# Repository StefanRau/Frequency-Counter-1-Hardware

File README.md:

# Frequency-Counter-1-hardware
This repository contains CAD data of Frequency Counter 1

Project repositories are:
- [Project](https://github.com/StefanRau/Frequency-Counter-1-Project)
- [Hardware](https://github.com/StefanRau/Frequency-Counter-1-Hardware)
- [Software](https://github.com/StefanRau/Frequency-Counter-1-Arduino)
- [PC terminal software](https://github.com/StefanRau/Frequency-Counter-1-Terminal)
## Main Board

## Front Plate

## 100 MHz TTL CMOS

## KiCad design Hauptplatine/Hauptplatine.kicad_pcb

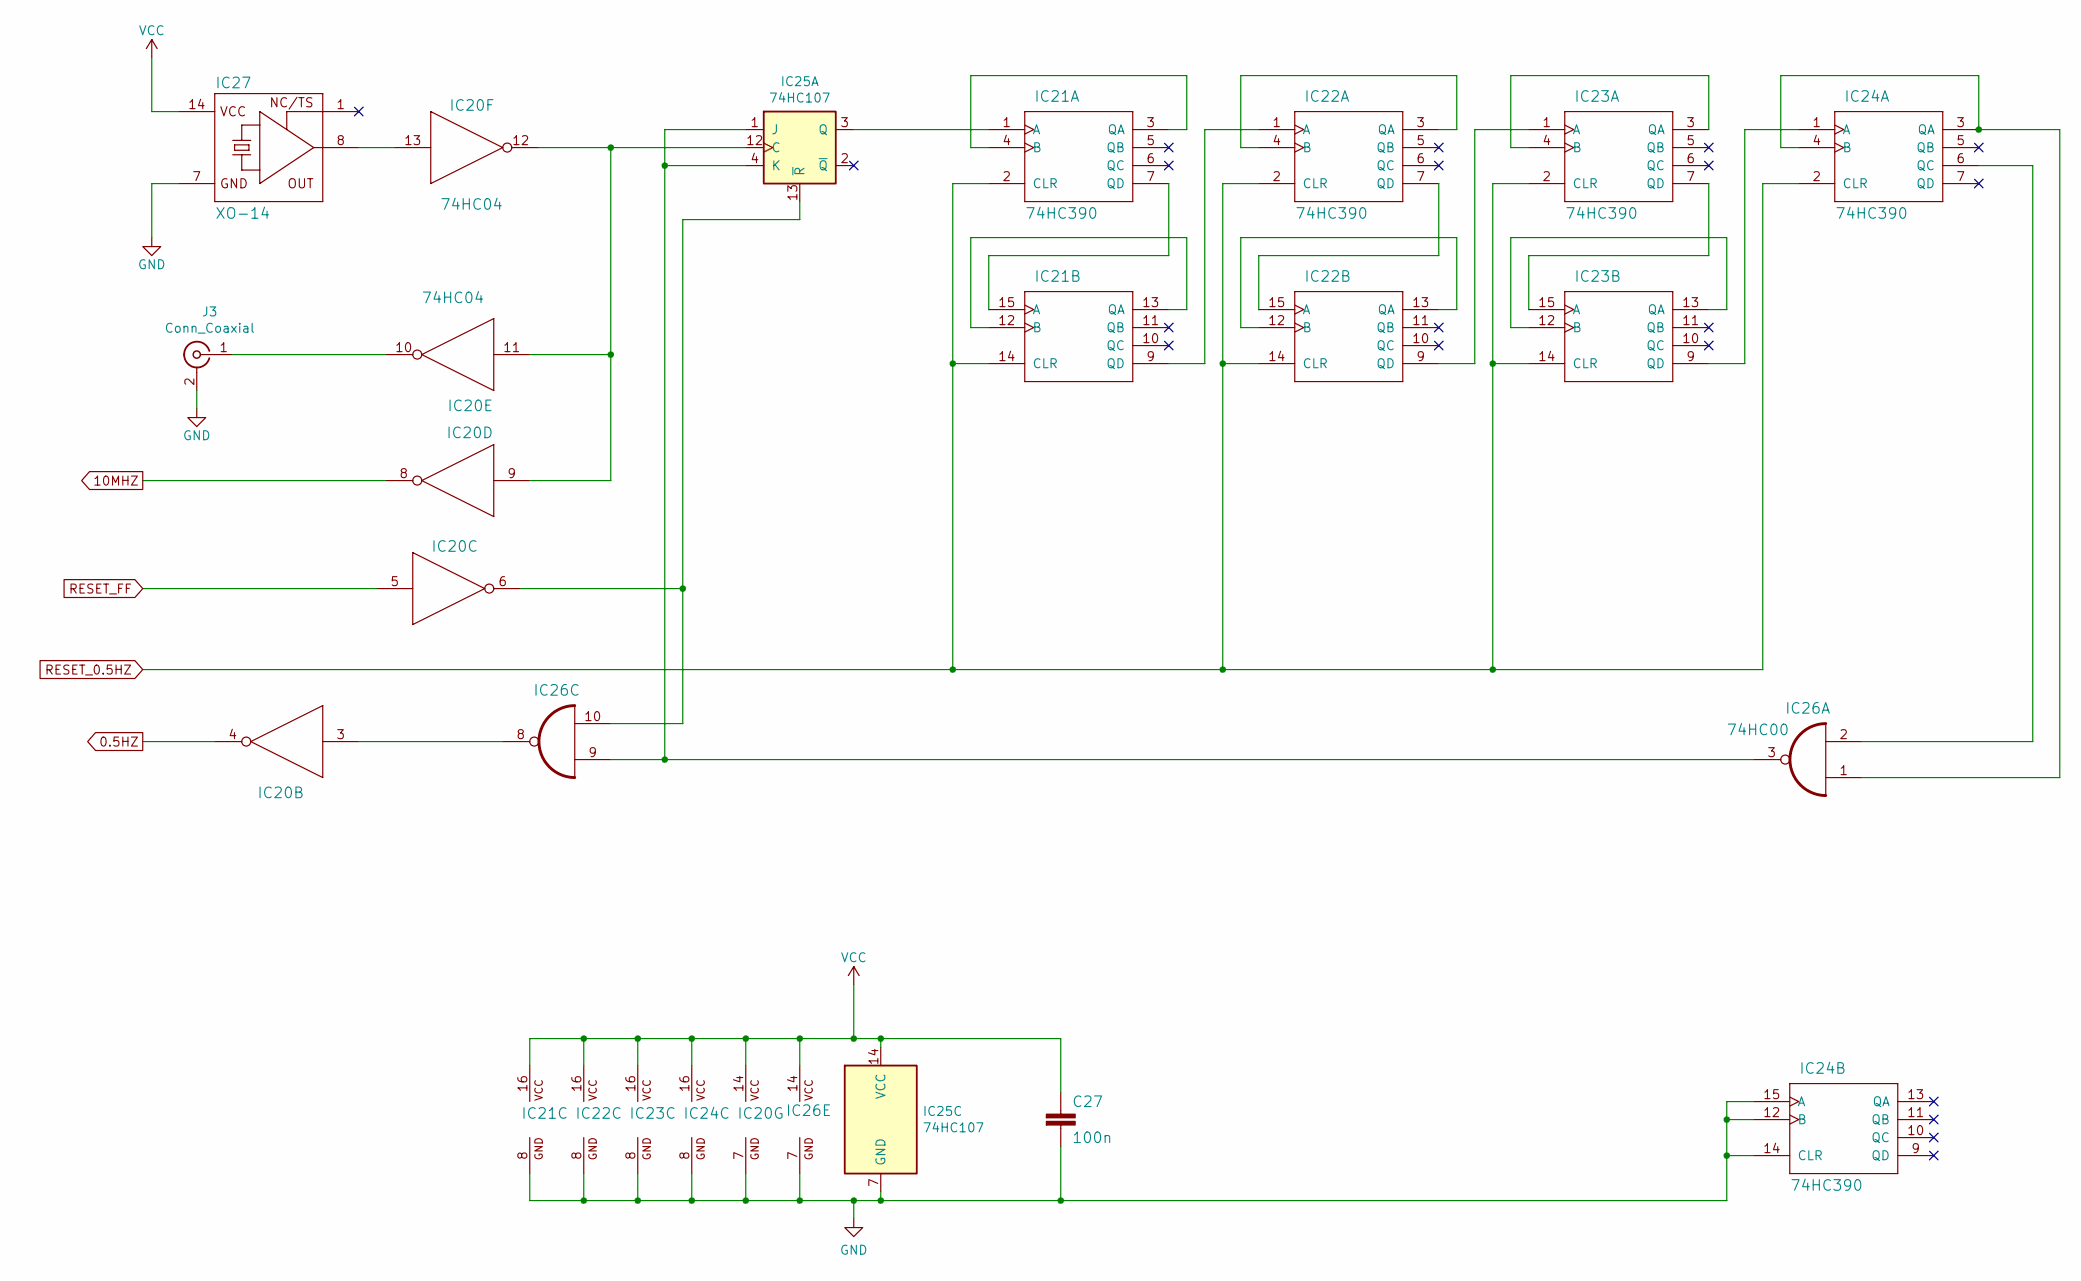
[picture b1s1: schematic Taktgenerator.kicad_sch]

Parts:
C27: 100n; C_Rect_L10.0mm_W4.0mm_P7.50mm_FKS3_FKP3
IC20: 74HC04; DIP-14_W7.62mm_LongPads
IC21, IC22, IC23, IC24: 74HC390; DIP-16_W7.62mm_LongPads
IC25: 74HC107; DIP-14_W7.62mm_LongPads
IC26: 74HC00; DIP-14_W7.62mm_LongPads
IC27: XO-14; Oscillator_DIP-14
J3: Conn_Coaxial; BNC_Amphenol_B6252HB-NPP3G-50_Horizontal

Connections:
0.5HZ: IC20.4 (O); also elsewhere on the board
10MHZ: IC20.8 (O); also elsewhere on the board
unnamed: IC20.3 (I), IC26.8 (O)
unnamed: IC20.6 (O), IC25.13 (~R), IC26.10 (I1)
unnamed: IC20.10 (O), J3.1 (In)
unnamed: IC20.9 (I), IC20.11 (I), IC20.12 (O), IC25.12 (C)
unnamed: IC20.13 (I), IC27.8 (OUT)
unnamed: IC21.1 (A), IC25.3 (Q)
unnamed: IC21.3 (QA), IC21.4 (B)
unnamed: IC21.9 (QD), IC22.1 (A)
unnamed: IC21.12 (B), IC21.13 (QA)
unnamed: IC21.7 (QD), IC21.15 (A)
unnamed: IC22.3 (QA), IC22.4 (B)
unnamed: IC22.9 (QD), IC23.1 (A)
unnamed: IC22.12 (B), IC22.13 (QA)
unnamed: IC22.7 (QD), IC22.15 (A)
unnamed: IC23.3 (QA), IC23.4 (B)
unnamed: IC23.9 (QD), IC24.1 (A)
unnamed: IC23.12 (B), IC23.13 (QA)
unnamed: IC23.7 (QD), IC23.15 (A)
unnamed: IC24.3 (QA), IC24.4 (B), IC26.1 (I0)
unnamed: IC24.6 (QC), IC26.2 (I1)
unnamed: IC25.1 (J), IC25.4 (K), IC26.3 (O), IC26.9 (I0)
RESET_0.5HZ: IC21.2 (CLR), IC21.14 (CLR), IC22.2 (CLR), IC22.14 (CLR), IC23.2 (CLR), IC23.14 (CLR), IC24.2 (CLR); also elsewhere on the board
RESET_FF: IC20.5 (I); also elsewhere on the board
VCC: C27.1, IC20.14 (VCC), IC21.16 (VCC), IC22.16 (VCC), IC23.16 (VCC), IC24.16 (VCC), IC25.14 (VCC), IC26.14 (VCC), IC27.14 (VCC); also elsewhere on the board

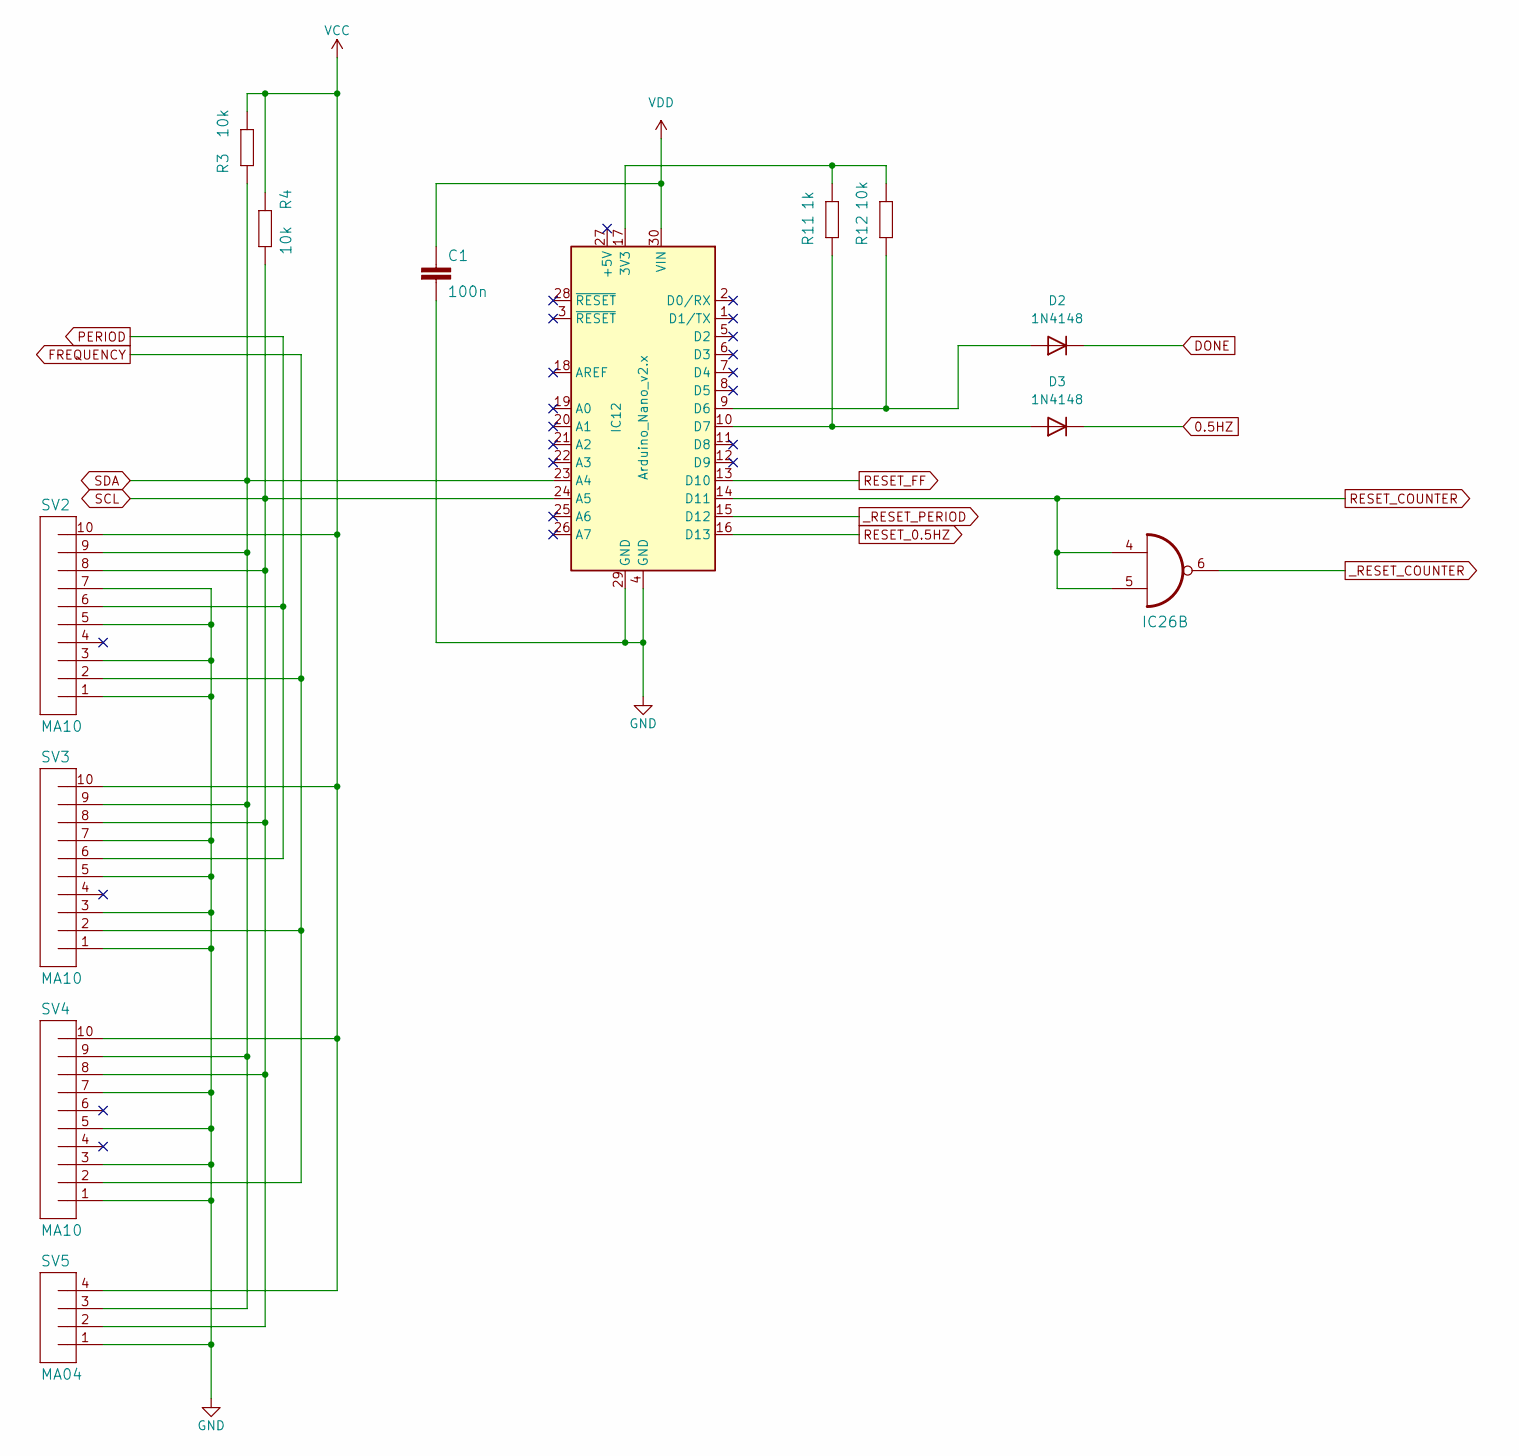
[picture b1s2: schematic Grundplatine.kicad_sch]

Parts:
C1: 100n; C_Rect_L10.0mm_W4.0mm_P7.50mm_FKS3_FKP3
D2, D3: 1N4148; D_DO-35_SOD27_P7.62mm_Horizontal
IC12: Arduino_Nano_v2.x; Arduino_Nano
IC26: 74HC00; DIP-14_W7.62mm_LongPads
R3, R4, R12: 10k; R_Axial_DIN0204_L3.6mm_D1.6mm_P1.90mm_Vertical
R11: 1k; R_Axial_DIN0204_L3.6mm_D1.6mm_P1.90mm_Vertical
SV2, SV3, SV4: MA10; PinSocket_1x10_P2.54mm_Vertical
SV5: MA04; PinSocket_1x04_P2.54mm_Vertical

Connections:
0.5HZ: D3.1 (K); also elsewhere on the board
DONE: D2.1 (K); also elsewhere on the board
FREQUENCY: SV2.2, SV3.2, SV4.2; also elsewhere on the board
unnamed: D2.2 (A), IC12.9 (D6), R12.1
unnamed: D3.2 (A), IC12.10 (D7), R11.1
unnamed: IC12.17 (3V3), R11.2, R12.2
PERIOD: SV2.6, SV3.6; also elsewhere on the board
RESET_0.5HZ: IC12.16 (D13); also elsewhere on the board
RESET_COUNTER: IC12.14 (D11), IC26.4 (I0), IC26.5 (I1); also elsewhere on the board
RESET_FF: IC12.13 (D10); also elsewhere on the board
SCL: IC12.24 (A5), R4.1, SV2.8, SV3.8, SV4.8, SV5.2; also elsewhere on the board
SDA: IC12.23 (A4), R3.1, SV2.9, SV3.9, SV4.9, SV5.3; also elsewhere on the board
VCC: R3.2, R4.2, SV2.10, SV3.10, SV4.10, SV5.4; also elsewhere on the board
VDD: C1.1, IC12.30 (VIN); also elsewhere on the board
_RESET_COUNTER: IC26.6 (O); also elsewhere on the board
_RESET_PERIOD: IC12.15 (D12); also elsewhere on the board

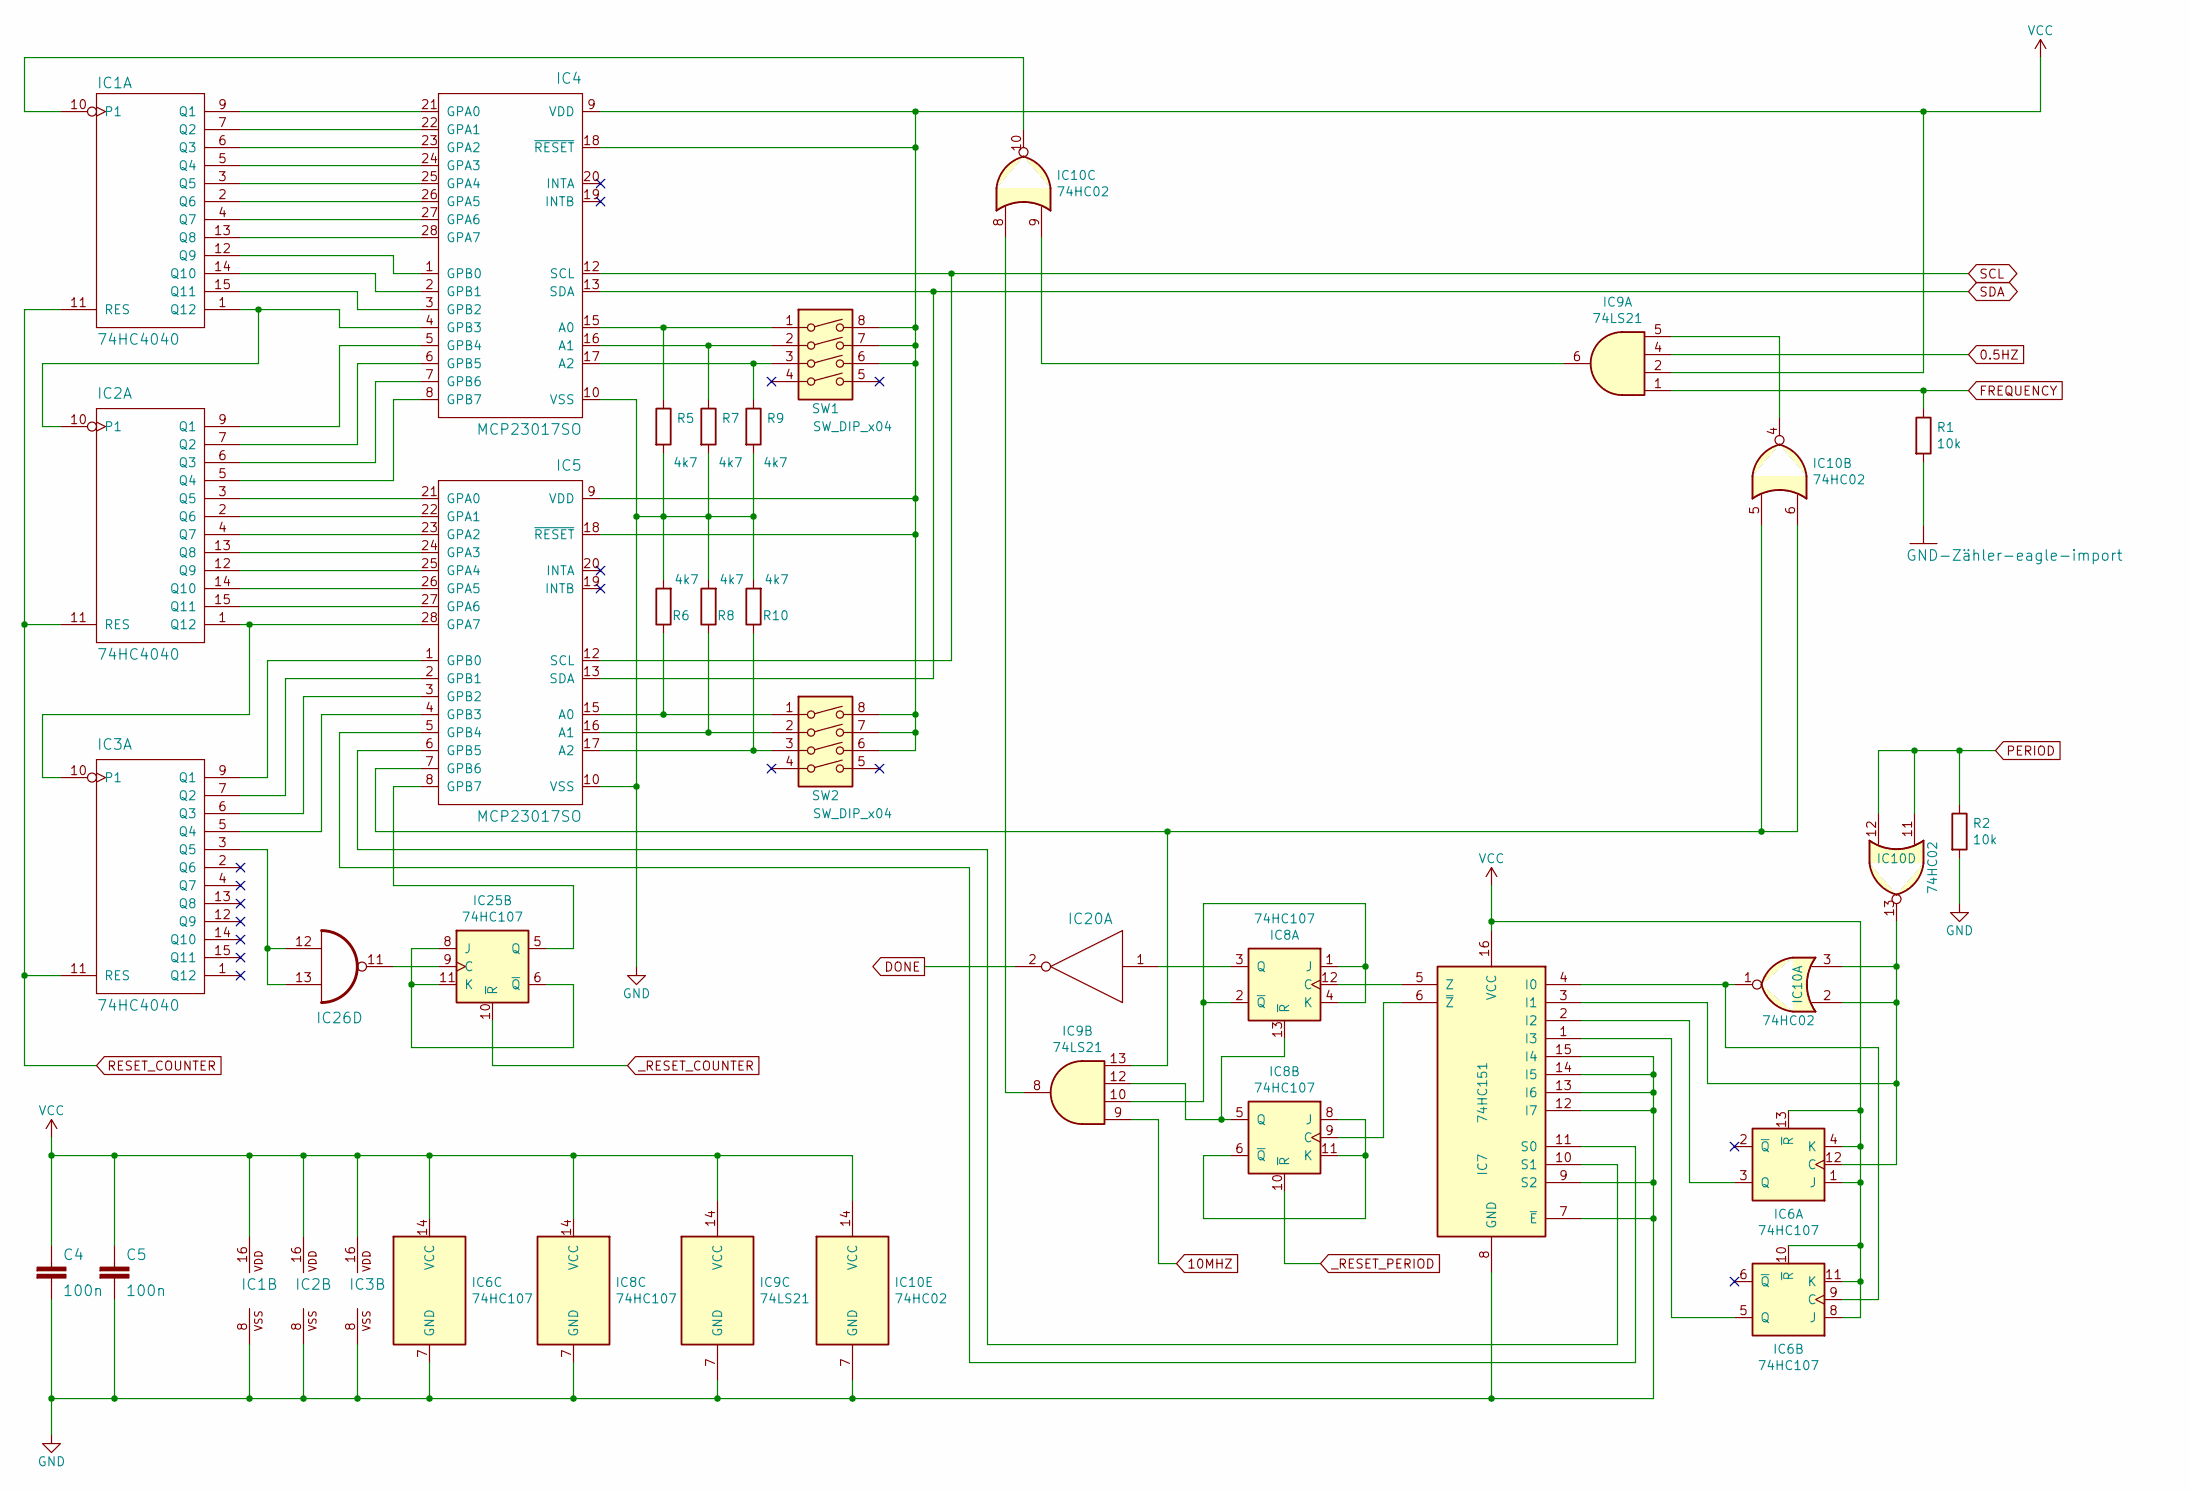
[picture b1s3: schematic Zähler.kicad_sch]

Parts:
C4, C5: 100n; C_Rect_L10.0mm_W4.0mm_P7.50mm_FKS3_FKP3
IC1, IC2, IC3: 74HC4040; DIP-16_W7.62mm_LongPads
IC4, IC5: MCP23017SO; DIP-28_W7.62mm_LongPads
IC6, IC8, IC25: 74HC107; DIP-14_W7.62mm_LongPads
IC7: 74HC151; DIP-16_W7.62mm_LongPads
IC9: 74LS21; DIP-14_W7.62mm_LongPads
IC10: 74HC02; DIP-14_W7.62mm_LongPads
IC20: 74HC04; DIP-14_W7.62mm_LongPads
IC26: 74HC00; DIP-14_W7.62mm_LongPads
R1, R2: 10k; R_Axial_DIN0207_L6.3mm_D2.5mm_P15.24mm_Horizontal
R5, R6, R7, R8, R9, R10: 4k7; R_Axial_DIN0204_L3.6mm_D1.6mm_P1.90mm_Vertical
SW1, SW2: SW_DIP_x04; SW_DIP_SPSTx04_Slide_9.78x12.34mm_W7.62mm_P2.54mm

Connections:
0.5HZ: IC9.4; also elsewhere on the board
10MHZ: IC9.9; also elsewhere on the board
DONE: IC20.2 (O); also elsewhere on the board
FREQUENCY: IC9.1, R1.1; also elsewhere on the board
unnamed: IC1.1 (Q12), IC2.10 (P1), IC4.4 (GPB3)
unnamed: IC1.2 (Q6), IC4.26 (GPA5)
unnamed: IC1.3 (Q5), IC4.25 (GPA4)
unnamed: IC1.4 (Q7), IC4.27 (GPA6)
unnamed: IC1.5 (Q4), IC4.24 (GPA3)
unnamed: IC1.6 (Q3), IC4.23 (GPA2)
unnamed: IC1.7 (Q2), IC4.22 (GPA1)
unnamed: IC1.9 (Q1), IC4.21 (GPA0)
unnamed: IC1.10 (P1), IC10.10
unnamed: IC1.12 (Q9), IC4.1 (GPB0)
unnamed: IC1.13 (Q8), IC4.28 (GPA7)
unnamed: IC1.14 (Q10), IC4.2 (GPB1)
unnamed: IC1.15 (Q11), IC4.3 (GPB2)
unnamed: IC2.1 (Q12), IC3.10 (P1), IC5.28 (GPA7)
unnamed: IC2.2 (Q6), IC5.22 (GPA1)
unnamed: IC2.3 (Q5), IC5.21 (GPA0)
unnamed: IC2.4 (Q7), IC5.23 (GPA2)
unnamed: IC2.5 (Q4), IC4.8 (GPB7)
unnamed: IC2.6 (Q3), IC4.7 (GPB6)
unnamed: IC2.7 (Q2), IC4.6 (GPB5)
unnamed: IC2.9 (Q1), IC4.5 (GPB4)
unnamed: IC2.12 (Q9), IC5.25 (GPA4)
unnamed: IC2.13 (Q8), IC5.24 (GPA3)
unnamed: IC2.14 (Q10), IC5.26 (GPA5)
unnamed: IC2.15 (Q11), IC5.27 (GPA6)
unnamed: IC3.5 (Q4), IC5.4 (GPB3)
unnamed: IC3.6 (Q3), IC5.3 (GPB2)
unnamed: IC3.7 (Q2), IC5.2 (GPB1)
unnamed: IC3.9 (Q1), IC5.1 (GPB0)
unnamed: IC4.15 (A0), R5.1, SW1.1
unnamed: IC4.16 (A1), R7.1, SW1.2
unnamed: IC4.17 (A2), R9.1, SW1.3
unnamed: IC5.5 (GPB4), IC7.11 (S0)
unnamed: IC5.6 (GPB5), IC7.10 (S1)
unnamed: IC5.15 (A0), R6.1, SW2.1
unnamed: IC5.16 (A1), R8.1, SW2.2
unnamed: IC5.17 (A2), R10.1, SW2.3
unnamed: IC6.3 (Q), IC7.2 (I2)
unnamed: IC6.5 (Q), IC7.1 (I3)
unnamed: IC7.5 (Z), IC8.12 (C)
unnamed: IC7.6 (~Z), IC8.9 (C)
unnamed: IC8.1 (J), IC8.2 (~Q), IC8.4 (K), IC9.10
unnamed: IC8.3 (Q), IC20.1 (I)
unnamed: IC8.6 (~Q), IC8.8 (J), IC8.11 (K)
unnamed: IC8.5 (Q), IC8.13 (~R), IC9.12
unnamed: IC6.9 (C), IC7.4 (I0), IC10.1
unnamed: IC9.5, IC10.4
unnamed: IC5.7 (GPB6), IC9.13, IC10.5, IC10.6
unnamed: IC9.8, IC10.8
unnamed: IC9.6, IC10.9
unnamed: IC6.12 (C), IC7.3 (I1), IC10.2, IC10.3, IC10.13
unnamed: IC5.8 (GPB7), IC25.5 (Q)
unnamed: IC25.9 (C), IC26.11 (O)
unnamed: IC25.6 (~Q), IC25.8 (J), IC25.11 (K)
unnamed: IC3.3 (Q5), IC26.12 (I0), IC26.13 (I1)
PERIOD: IC10.11, IC10.12, R2.1; also elsewhere on the board
RESET_COUNTER: IC1.11 (RES), IC2.11 (RES), IC3.11 (RES); also elsewhere on the board
SCL: IC4.12 (SCL), IC5.12 (SCL); also elsewhere on the board
SDA: IC4.13 (SDA), IC5.13 (SDA); also elsewhere on the board
VCC: C4.1, C5.1, IC1.16 (VDD), IC2.16 (VDD), IC3.16 (VDD), IC4.9 (VDD), IC4.18 (~RESET), IC5.9 (VDD), IC5.18 (~RESET), IC6.1 (J), IC6.4 (K), IC6.8 (J), IC6.10 (~R), IC6.11 (K), IC6.13 (~R), IC6.14 (VCC), IC7.16 (VCC), IC8.14 (VCC), IC9.2, IC9.14 (VCC), IC10.14 (VCC), SW1.6, SW1.7, SW1.8, SW2.6, SW2.7, SW2.8; also elsewhere on the board
_RESET_COUNTER: IC25.10 (~R); also elsewhere on the board
_RESET_PERIOD: IC8.10 (~R); also elsewhere on the board

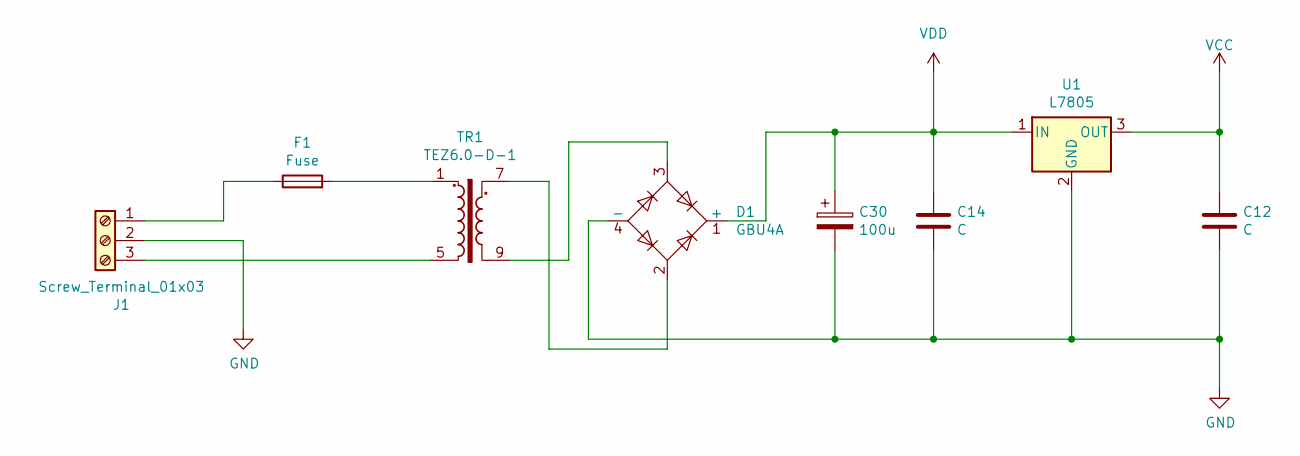
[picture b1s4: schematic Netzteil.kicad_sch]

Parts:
C12, C14: C; C_Rect_L10.0mm_W4.0mm_P7.50mm_FKS3_FKP3
C30: 100u; CP_Radial_D13.0mm_P5.00mm
D1: GBU4A; Diode_Bridge_Vishay_GBU
F1: Fuse; Fuseholder_Cylinder-5x20mm_Schurter_0031_8201_Horizontal_Op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
J1: Screw_Terminal_01x03; TerminalBlock_Phoenix_MKDS-1,5-3-5.08_1x03_P5.08mm_Horizont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
TR1: TEZ6.0-D-1; Transformer_Breve_TEZ-38x45
U1: L7805; TO-220-3_Vertical

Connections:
unnamed: D1.2, TR1.7
unnamed: D1.3, TR1.9
unnamed: F1.1, J1.1
unnamed: F1.2, TR1.1
unnamed: J1.3, TR1.5
VCC: C12.1, U1.3 (OUT); also elsewhere on the board
VDD: C14.1, C30.1, D1.1 (+), U1.1 (IN); also elsewhere on the board

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
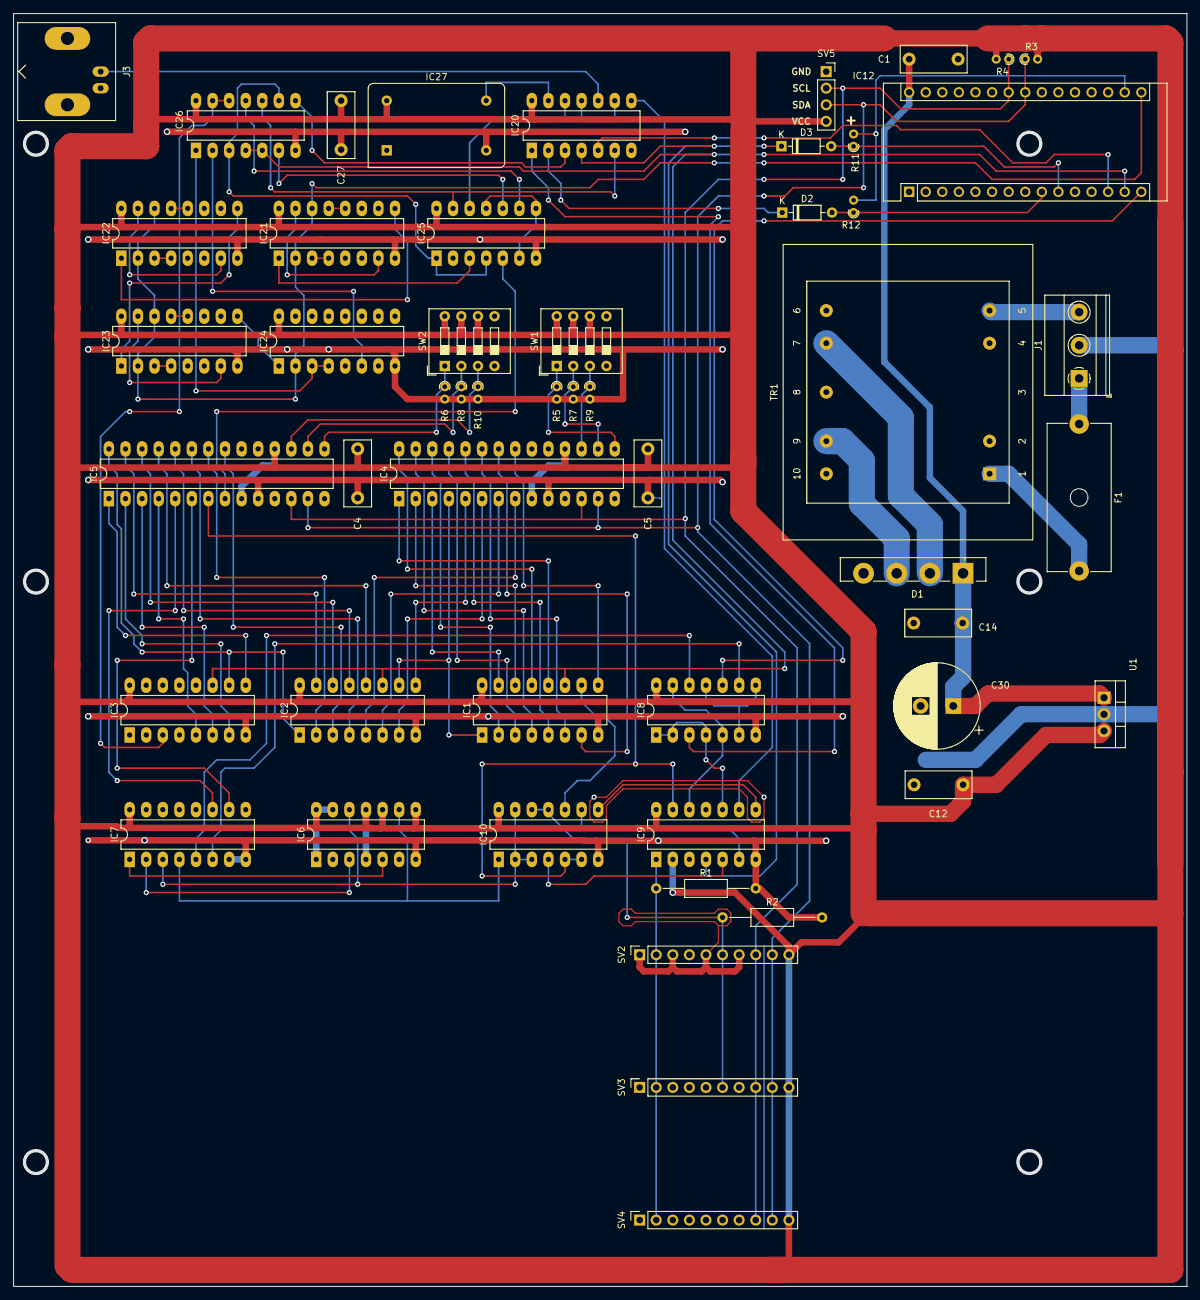
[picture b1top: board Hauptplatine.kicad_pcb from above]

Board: 2 copper layers, 179.7 x 194.9 mm, 52 parts (0 on the bottom side), 99 nets.

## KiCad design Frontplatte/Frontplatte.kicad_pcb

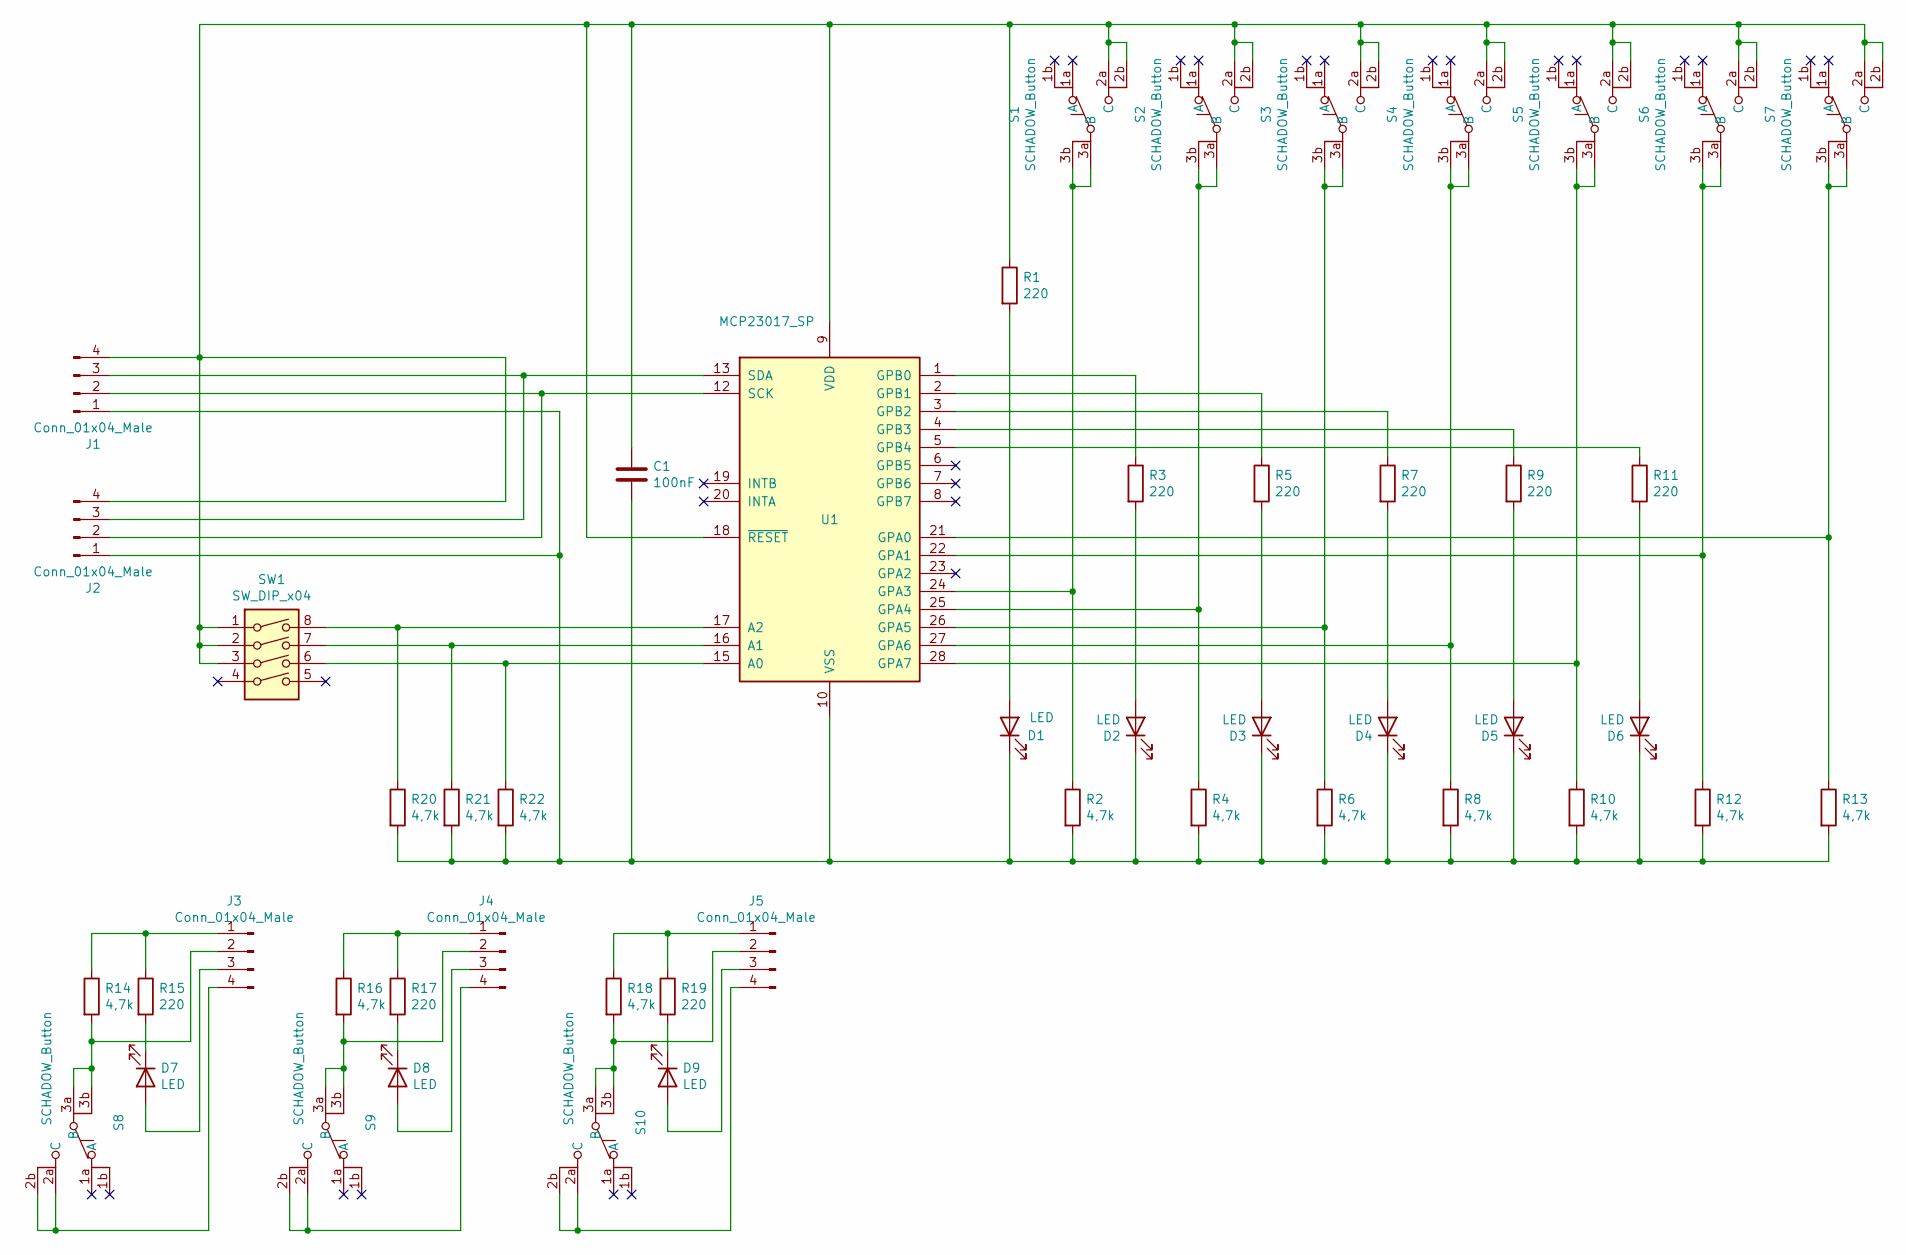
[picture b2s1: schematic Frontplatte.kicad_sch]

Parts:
C1: 100nF; C_Rect_L10.0mm_W4.0mm_P7.50mm_FKS3_FKP3
D1, D2, D3, D4, D5, D6, D7, D8, D9: LED; LED_D5.0mm
J1, J2, J3, J4, J5: Conn_01x04_Male; PinHeader_1x04_P2.54mm_Vertical
R1, R3, R5, R7, R9, R11: 220; R_Axial_DIN0204_L3.6mm_D1.6mm_P7.62mm_Horizontal
R2, R4, R6, R8, R10: 4,7k; R_Axial_DIN0207_L6.3mm_D2.5mm_P15.24mm_Horizontal
R12, R13, R20, R21, R22: 4,7k; R_Axial_DIN0204_L3.6mm_D1.6mm_P7.62mm_Horizontal
R14, R16, R18: 4,7k; R_Axial_DIN0204_L3.6mm_D1.6mm_P1.90mm_Vertical
R15, R17, R19: 220; R_Axial_DIN0204_L3.6mm_D1.6mm_P1.90mm_Vertical
S1, S2, S3, S4, S5, S6, S7, S8, S9, S10: SCHADOW_Button
SW1: SW_DIP_x04; SW_DIP_SPSTx04_Slide_9.78x12.34mm_W7.62mm_P2.54mm
U1: MCP23017_SP; DIP-28_W7.62mm_LongPads

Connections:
unnamed: C1.1, J1.4, J2.4, R1.1, S1.2a (C), S1.2b, S2.2a (C), S2.2b, S3.2a (C), S3.2b, S4.2a (C), S4.2b, S5.2a (C), S5.2b, S6.2a (C), S6.2b, S7.2a (C), S7.2b, SW1.1, SW1.2, SW1.3, U1.9 (VDD), U1.18 (~RESET)
unnamed: C1.2, D1.1 (K), D2.1 (K), D3.1 (K), D4.1 (K), D5.1 (K), D6.1 (K), J1.1, J2.1, R2.2, R4.2, R6.2, R8.2, R10.2, R12.2, R13.2, R20.2, R21.2, R22.2, U1.10 (VSS)
unnamed: D1.2 (A), R1.2
unnamed: D2.2 (A), R3.2
unnamed: D3.2 (A), R5.2
unnamed: D4.2 (A), R7.2
unnamed: D5.2 (A), R9.2
unnamed: D6.2 (A), R11.2
unnamed: D7.1 (K), R15.2
unnamed: D7.2 (A), J3.3
unnamed: D8.1 (K), R17.2
unnamed: D8.2 (A), J4.3
unnamed: D9.1 (K), R19.2
unnamed: D9.2 (A), J5.3
unnamed: J1.2, J2.2, U1.12 (SCK)
unnamed: J1.3, J2.3, U1.13 (SDA)
unnamed: J3.1, R14.1, R15.1
unnamed: J3.2, R14.2, S8.3a (B), S8.3b
unnamed: J3.4, S8.2a (C), S8.2b
unnamed: J4.1, R16.1, R17.1
unnamed: J4.2, R16.2, S9.3a (B), S9.3b
unnamed: J4.4, S9.2a (C), S9.2b
unnamed: J5.1, R18.1, R19.1
unnamed: J5.2, R18.2, S10.3a (B), S10.3b
unnamed: J5.4, S10.2a (C), S10.2b
unnamed: R2.1, S1.3a (B), S1.3b, U1.24 (GPA3)
unnamed: R3.1, U1.1 (GPB0)
unnamed: R4.1, S2.3a (B), S2.3b, U1.25 (GPA4)
unnamed: R5.1, U1.2 (GPB1)
unnamed: R6.1, S3.3a (B), S3.3b, U1.26 (GPA5)
unnamed: R7.1, U1.3 (GPB2)
unnamed: R8.1, S4.3a (B), S4.3b, U1.27 (GPA6)
unnamed: R9.1, U1.4 (GPB3)
unnamed: R10.1, S5.3a (B), S5.3b, U1.28 (GPA7)
unnamed: R11.1, U1.5 (GPB4)
unnamed: R12.1, S6.3a (B), S6.3b, U1.22 (GPA1)
unnamed: R13.1, S7.3a (B), S7.3b, U1.21 (GPA0)
unnamed: R20.1, SW1.8, U1.17 (A2)
unnamed: R21.1, SW1.7, U1.16 (A1)
unnamed: R22.1, SW1.6, U1.15 (A0)

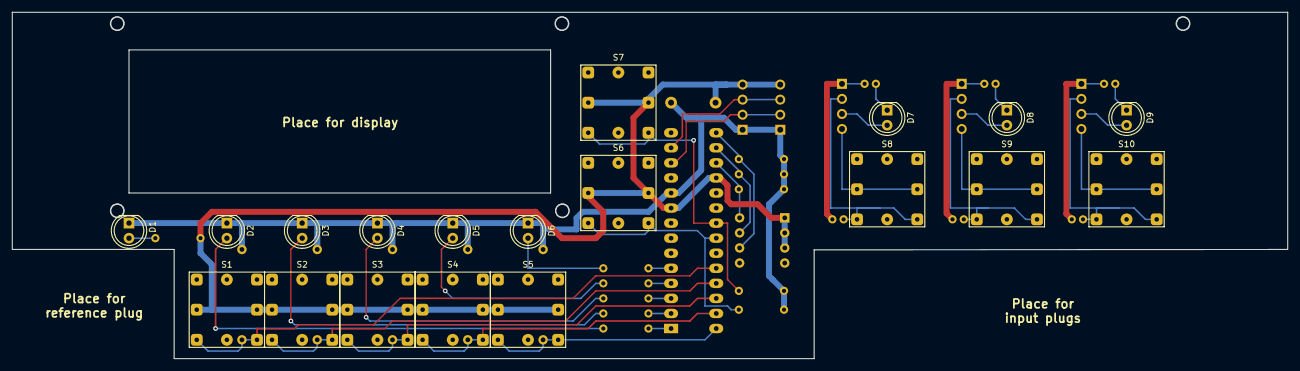
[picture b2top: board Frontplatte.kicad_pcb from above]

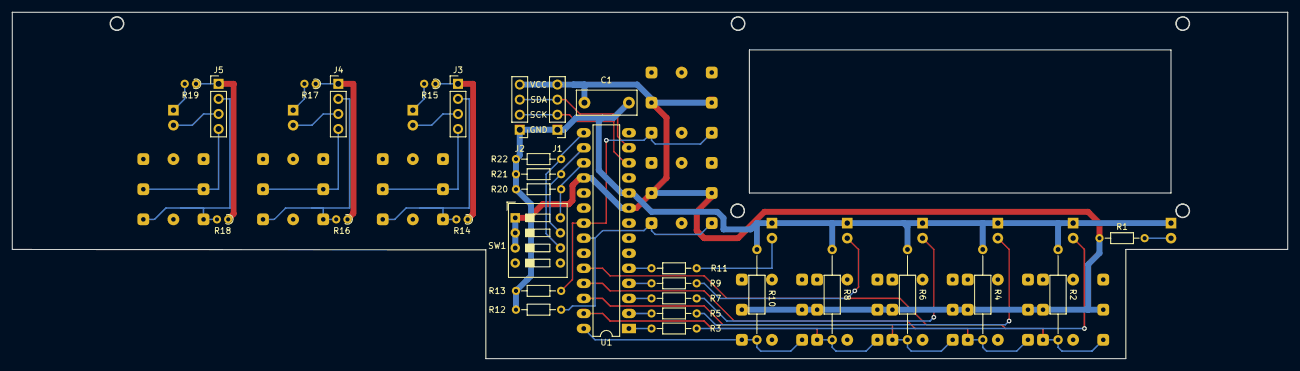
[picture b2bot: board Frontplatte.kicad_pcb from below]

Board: 2 copper layers, 215.1 x 58.4 mm, 49 parts (30 on the bottom side), 40 nets.
